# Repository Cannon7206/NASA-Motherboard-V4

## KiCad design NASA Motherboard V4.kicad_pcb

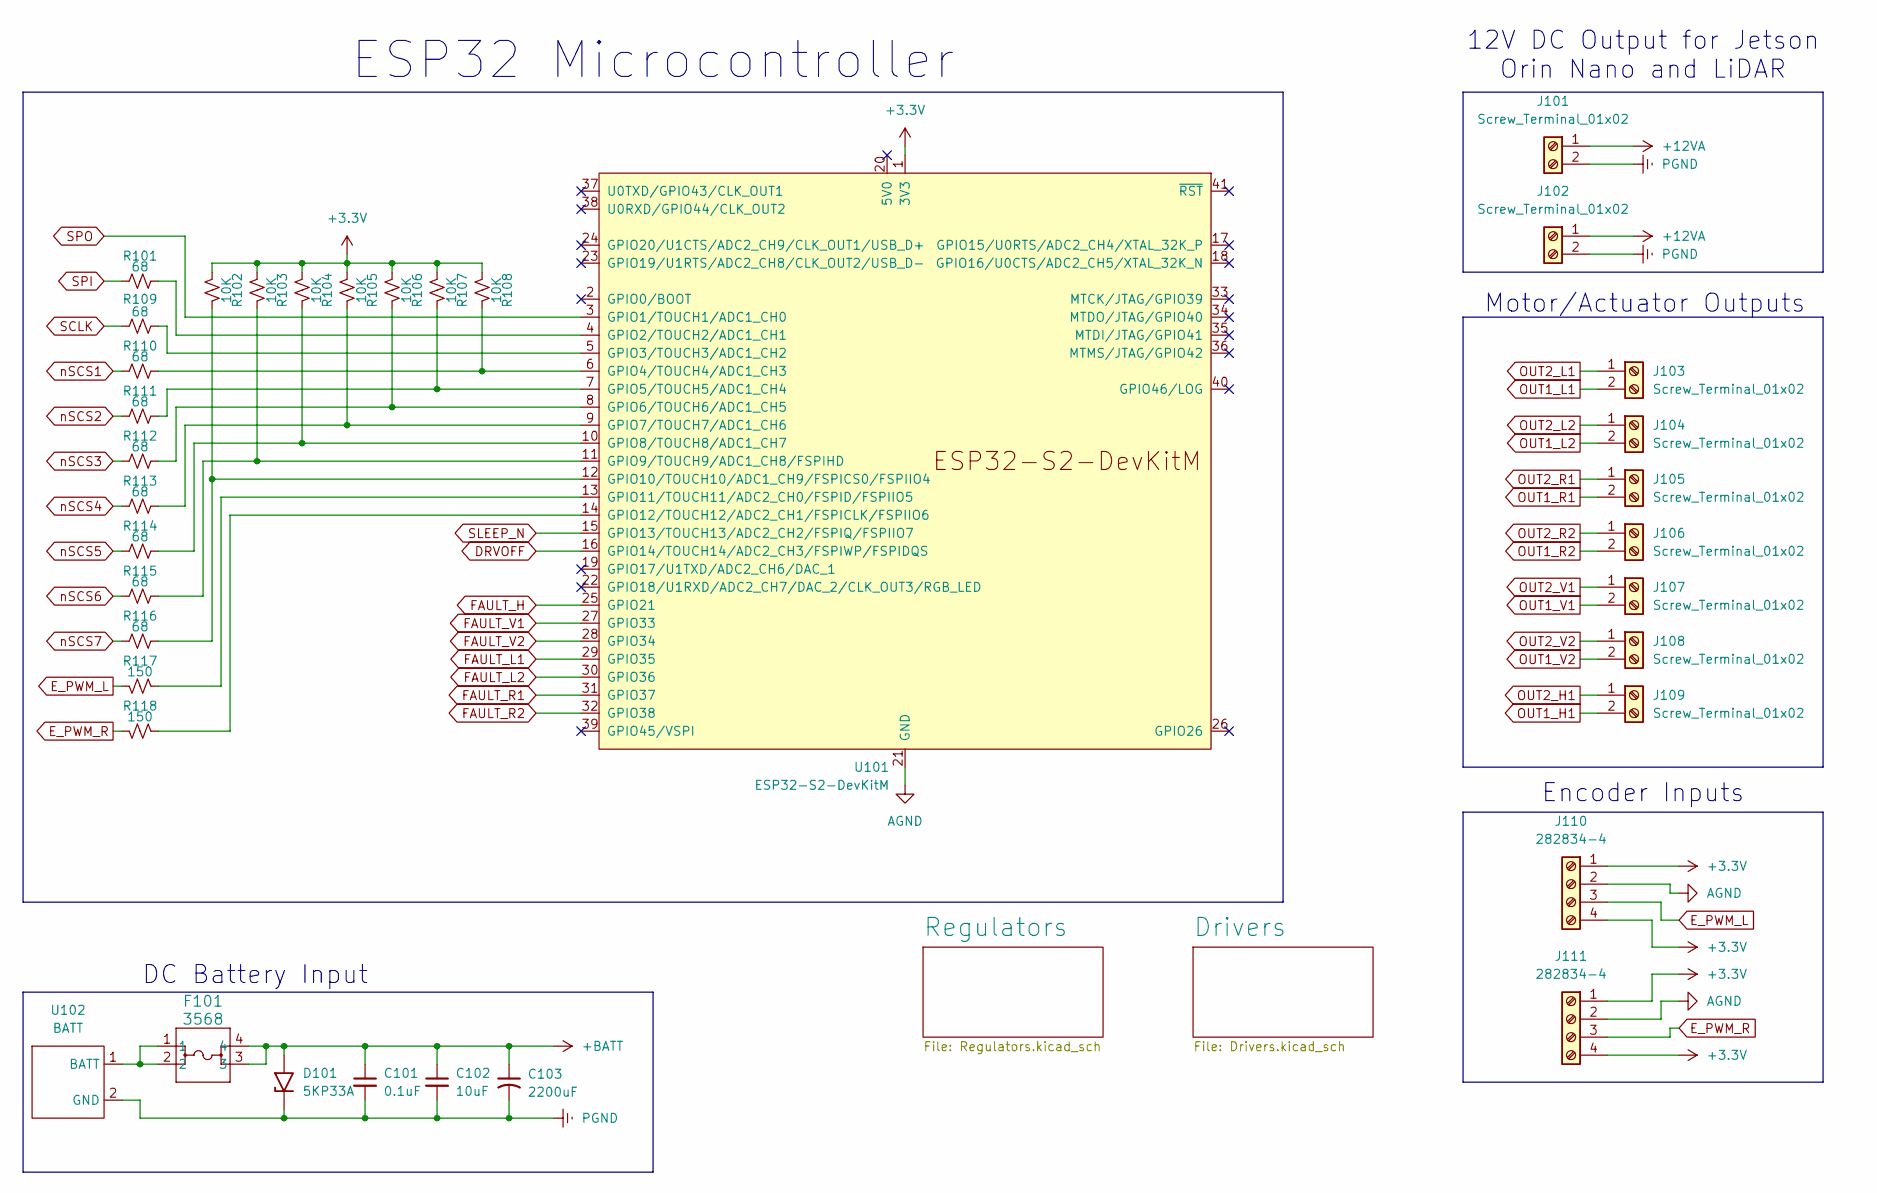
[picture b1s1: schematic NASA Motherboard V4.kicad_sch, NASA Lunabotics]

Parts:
C101: 0.1uF; C_0402_1005Metric_Pad0.74x0.62mm_HandSolder
C102: 10uF; C_1206_3216Metric_Pad1.33x1.80mm_HandSolder
C103: 2200uF; CP_Radial_D16.0mm_P7.50mm
D101: 5KP33A; D_P600_R-6_P20.00mm_Horizontal
F101: 3568; 3568_KEY
J101, J102: Screw_Terminal_01x02; TerminalBlock_TE_282834-2_1x02_P2.54mm_Horizontal; MFR Part # 282834-2
J103, J104, J105, J106, J107, J108, J109: Screw_Terminal_01x02; TerminalBlock_TE_282834-2_1x02_P2.54mm_Horizontal
J110, J111: 282834-4; TerminalBlock_TE_282834-4_1x04_P2.54mm_Horizontal; MFR Part # 282834-4
R101, R109, R110, R111, R112, R113, R114, R115, R116: 68; R_0402_1005Metric_Pad0.72x0.64mm_HandSolder
R102, R103, R104, R105, R106, R107, R108: 10K; R_0603_1608Metric_Pad0.98x0.95mm_HandSolder
R117, R118: 150; R_0603_1608Metric_Pad0.98x0.95mm_HandSolder
U101: ESP32-S2-DevKitM
U102: BATT; Battery Input

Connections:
+3.3V: J110.1, J110.4, J111.1, J111.4, R102.2, R103.2, R104.2, R105.2, R106.2, R107.2, R108.2, U101.1 (3V3); also elsewhere on the board
+12VA: J101.1, J102.1; also elsewhere on the board
+BATT: C101.1, C102.1, C103.1, D101.2 (A2), F101.3, F101.4; also elsewhere on the board
AGND: J110.2, J111.2, U101.21 (GND), U101.42 (GND); also elsewhere on the board
DRVOFF: U101.16 (GPIO14/TOUCH14/ADC2_CH3/FSPIWP/FSPIDQS); also elsewhere on the board
E_PWM_L: J110.3, R117.2
E_PWM_R: J111.3, R118.2
FAULT_H: U101.25 (GPIO21); also elsewhere on the board
FAULT_L1: U101.29 (GPIO35); also elsewhere on the board
FAULT_L2: U101.30 (GPIO36); also elsewhere on the board
FAULT_R1: U101.31 (GPIO37); also elsewhere on the board
FAULT_R2: U101.32 (GPIO38); also elsewhere on the board
FAULT_V1: U101.27 (GPIO33); also elsewhere on the board
FAULT_V2: U101.28 (GPIO34); also elsewhere on the board
unnamed: R101.2, U101.4 (GPIO2/TOUCH2/ADC1_CH1)
unnamed: R109.2, U101.5 (GPIO3/TOUCH3/ADC1_CH2)
unnamed: R108.1, R110.2, U101.6 (GPIO4/TOUCH4/ADC1_CH3)
unnamed: R107.1, R111.2, U101.7 (GPIO5/TOUCH5/ADC1_CH4)
unnamed: R106.1, R112.2, U101.8 (GPIO6/TOUCH6/ADC1_CH5)
unnamed: R105.1, R113.2, U101.9 (GPIO7/TOUCH7/ADC1_CH6)
unnamed: R104.1, R114.2, U101.10 (GPIO8/TOUCH8/ADC1_CH7)
unnamed: R103.1, R115.2, U101.11 (GPIO9/TOUCH9/ADC1_CH8/FSPIHD)
unnamed: R102.1, R116.2, U101.12 (GPIO10/TOUCH10/ADC1_CH9/FSPICS0/FSPIIO4)
unnamed: R117.1, U101.13 (GPIO11/TOUCH11/ADC2_CH0/FSPID/FSPIIO5)
unnamed: R118.1, U101.14 (GPIO12/TOUCH12/ADC2_CH1/FSPICLK/FSPIIO6)
unnamed: F101.1, F101.2, U102.1 (BATT)
OUT1_H1: J109.2; also elsewhere on the board
OUT1_L1: J103.2; also elsewhere on the board
OUT1_L2: J104.2; also elsewhere on the board
OUT1_R1: J105.2; also elsewhere on the board
OUT1_R2: J106.2; also elsewhere on the board
OUT1_V1: J107.2; also elsewhere on the board
OUT1_V2: J108.2; also elsewhere on the board
OUT2_H1: J109.1; also elsewhere on the board
OUT2_L1: J103.1; also elsewhere on the board
OUT2_L2: J104.1; also elsewhere on the board
OUT2_R1: J105.1; also elsewhere on the board
OUT2_R2: J106.1; also elsewhere on the board
OUT2_V1: J107.1; also elsewhere on the board
OUT2_V2: J108.1; also elsewhere on the board
PGND: C101.2, C102.2, C103.2, D101.1 (A1), J101.2, J102.2, U102.2 (GND); also elsewhere on the board
SCLK: R109.1; also elsewhere on the board
SLEEP_N: U101.15 (GPIO13/TOUCH13/ADC2_CH2/FSPIQ/FSPIIO7); also elsewhere on the board
SPI: R101.1; also elsewhere on the board
SPO: U101.3 (GPIO1/TOUCH1/ADC1_CH0); also elsewhere on the board
nSCS1: R110.1; also elsewhere on the board
nSCS2: R111.1; also elsewhere on the board
nSCS3: R112.1; also elsewhere on the board
nSCS4: R113.1; also elsewhere on the board
nSCS5: R114.1; also elsewhere on the board
nSCS6: R115.1; also elsewhere on the board
nSCS7: R116.1; also elsewhere on the board

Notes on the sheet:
Encoder Inputs
DC Battery Input
12V DC Output for Jetson Orin Nano and LiDAR
Motor/Actuator Outputs
ESP32 Microcontroller

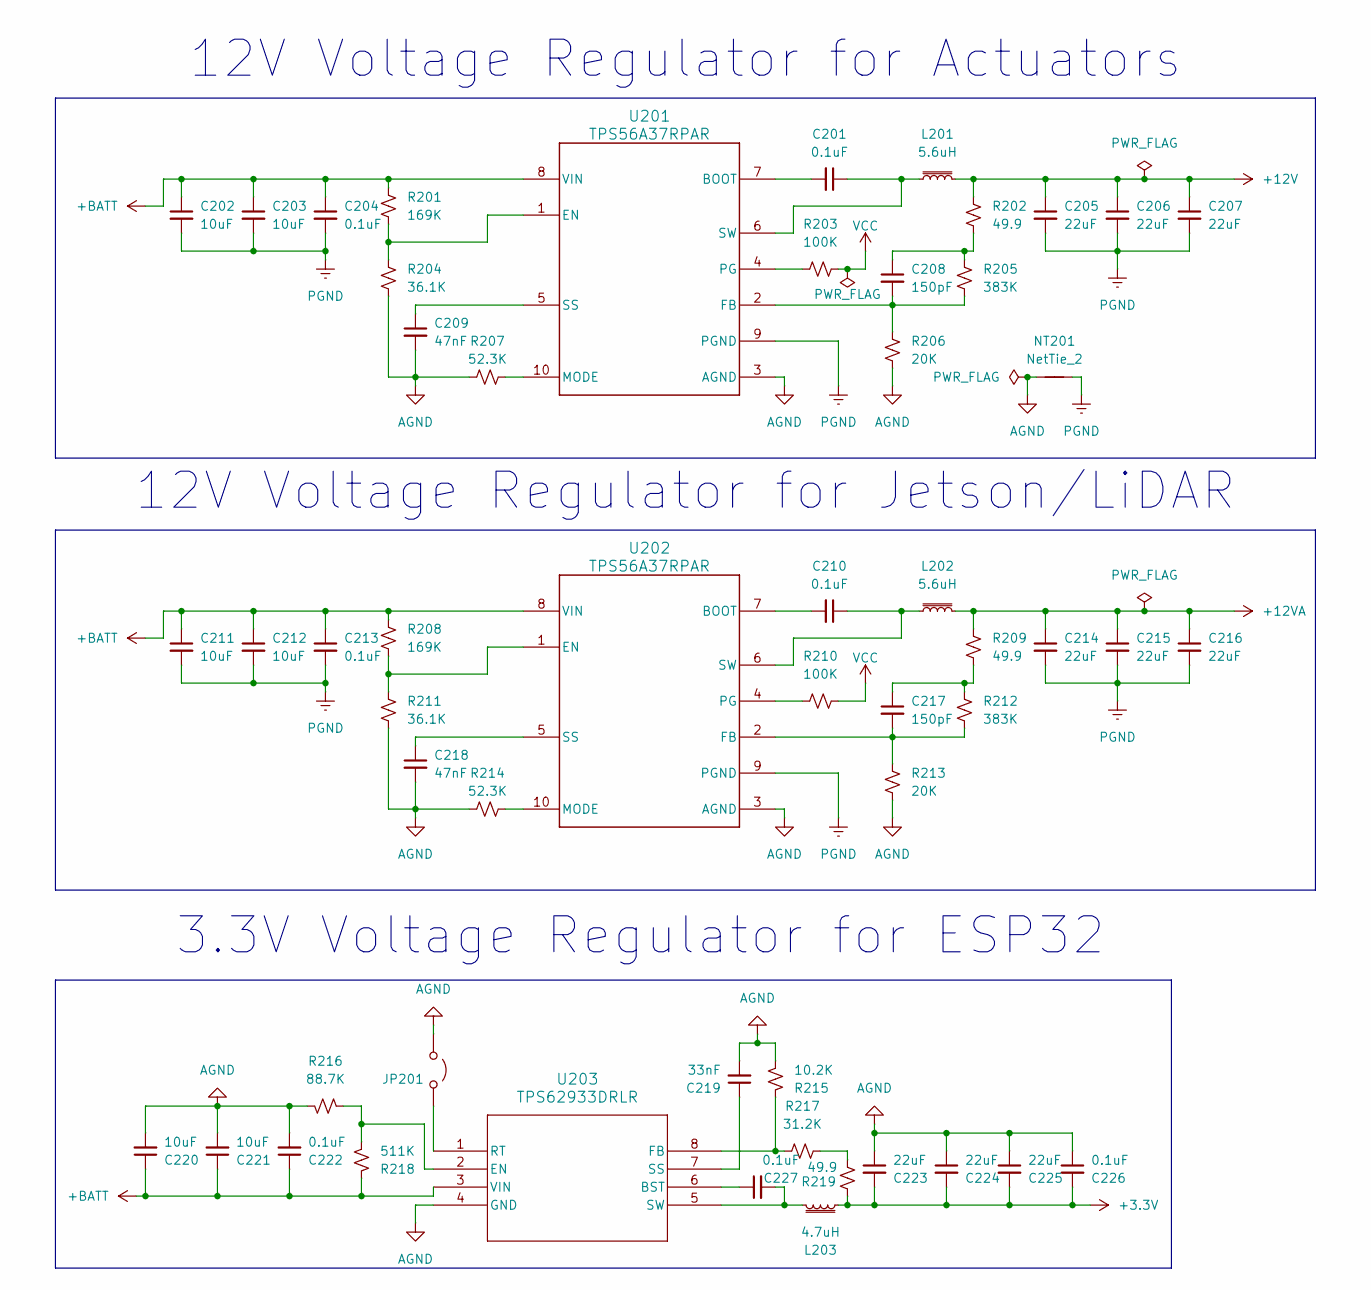
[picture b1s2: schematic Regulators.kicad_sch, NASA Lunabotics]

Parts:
C201, C204, C210, C213, C222, C226, C227: 0.1uF; C_0402_1005Metric_Pad0.74x0.62mm_HandSolder
C202, C203, C211, C212, C220, C221: 10uF; C_1206_3216Metric_Pad1.33x1.80mm_HandSolder
C205, C206, C207, C214, C215, C216, C223, C224, C225: 22uF; C_1210_3225Metric_Pad1.33x2.70mm_HandSolder
C208, C217: 150pF; C_0402_1005Metric_Pad0.74x0.62mm_HandSolder
C209, C218: 47nF; C_0603_1608Metric_Pad1.08x0.95mm_HandSolder
C219: 33nF; C_0603_1608Metric_Pad1.08x0.95mm_HandSolder
JP201: Jumper_2_Open; SolderJumper-2_P1.3mm_Open_Pad1.0x1.5mm
L201, L202: 5.6uH; IND_IHLP-6767DZ_VIS-M
L203: 4.7uH; IND_SRP6530A_BRN-M
NT201: NetTie_2; NetTie-2_THT_Pad1.0mm
R201, R208: 169K; R_0603_1608Metric_Pad0.98x0.95mm_HandSolder
R202, R209, R219: 49.9; R_0402_1005Metric_Pad0.72x0.64mm_HandSolder
R203, R210: 100K; R_0603_1608Metric_Pad0.98x0.95mm_HandSolder
R204, R211: 36.1K; R_0603_1608Metric_Pad0.98x0.95mm_HandSolder
R205, R212: 383K; R_0603_1608Metric_Pad0.98x0.95mm_HandSolder
R206, R213: 20K; R_0603_1608Metric_Pad0.98x0.95mm_HandSolder
R207, R214: 52.3K; R_0603_1608Metric_Pad0.98x0.95mm_HandSolder
R215: 10.2K; R_0603_1608Metric_Pad0.98x0.95mm_HandSolder
R216: 88.7K; R_0603_1608Metric_Pad0.98x0.95mm_HandSolder
R217: 31.2K; R_0603_1608Metric_Pad0.98x0.95mm_HandSolder
R218: 511K; R_0603_1608Metric_Pad0.98x0.95mm_HandSolder
U201, U202: TPS56A37RPAR; RPA0010A-MFG
U203: TPS62933DRLR; SOT-5X3-8_DRL_TEX

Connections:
+3.3V: C223.2, C224.2, C225.2, C226.2, L203.2, R219.1; also elsewhere on the board
+12V: C205.1, C206.1, C207.1, L201.2, R202.1; also elsewhere on the board
+12VA: C214.1, C215.1, C216.1, L202.2, R209.1; also elsewhere on the board
+BATT: C202.1, C203.1, C204.1, C211.1, C212.1, C213.1, C220.1, C221.1, C222.1, R201.1, R208.1, R218.1, U201.8 (VIN), U202.8 (VIN), U203.3 (VIN); also elsewhere on the board
AGND: C209.2, C218.2, C219.2, C220.2, C221.2, C222.2, C223.1, C224.1, C225.1, C226.1, JP201.1 (A), NT201.1, R204.2, R206.2, R207.2, R211.2, R213.2, R214.2, R215.2, R216.2, U201.3 (AGND), U202.3 (AGND), U203.4 (GND); also elsewhere on the board
unnamed: C208.1, R202.2, R205.1
unnamed: C217.1, R209.2, R212.1
unnamed: JP201.2 (B), U203.1 (RT)
unnamed: R217.2, R219.2
unnamed: C201.2, U201.7 (BOOT)
unnamed: R201.2, R204.1, U201.1 (EN)
unnamed: C208.2, R205.2, R206.1, U201.2 (FB)
unnamed: R207.1, U201.10 (MODE)
unnamed: R203.1, U201.4 (PG)
unnamed: C209.1, U201.5 (SS)
unnamed: C201.1, L201.1, U201.6 (SW)
unnamed: C210.2, U202.7 (BOOT)
unnamed: R208.2, R211.1, U202.1 (EN)
unnamed: C217.2, R212.2, R213.1, U202.2 (FB)
unnamed: R214.1, U202.10 (MODE)
unnamed: R210.1, U202.4 (PG)
unnamed: C218.1, U202.5 (SS)
unnamed: C210.1, L202.1, U202.6 (SW)
unnamed: C227.1, U203.6 (BST)
unnamed: R216.1, R218.2, U203.2 (EN)
unnamed: R215.1, R217.1, U203.8 (FB)
unnamed: C219.1, U203.7 (SS)
unnamed: C227.2, L203.1, U203.5 (SW)
PGND: C202.2, C203.2, C204.2, C205.2, C206.2, C207.2, C211.2, C212.2, C213.2, C214.2, C215.2, C216.2, NT201.2, U201.9 (PGND), U202.9 (PGND); also elsewhere on the board
VCC: R203.2, R210.2

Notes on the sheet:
12V Voltage Regulator for Actuators
3.3V Voltage Regulator for ESP32
12V Voltage Regulator for Jetson/LiDAR

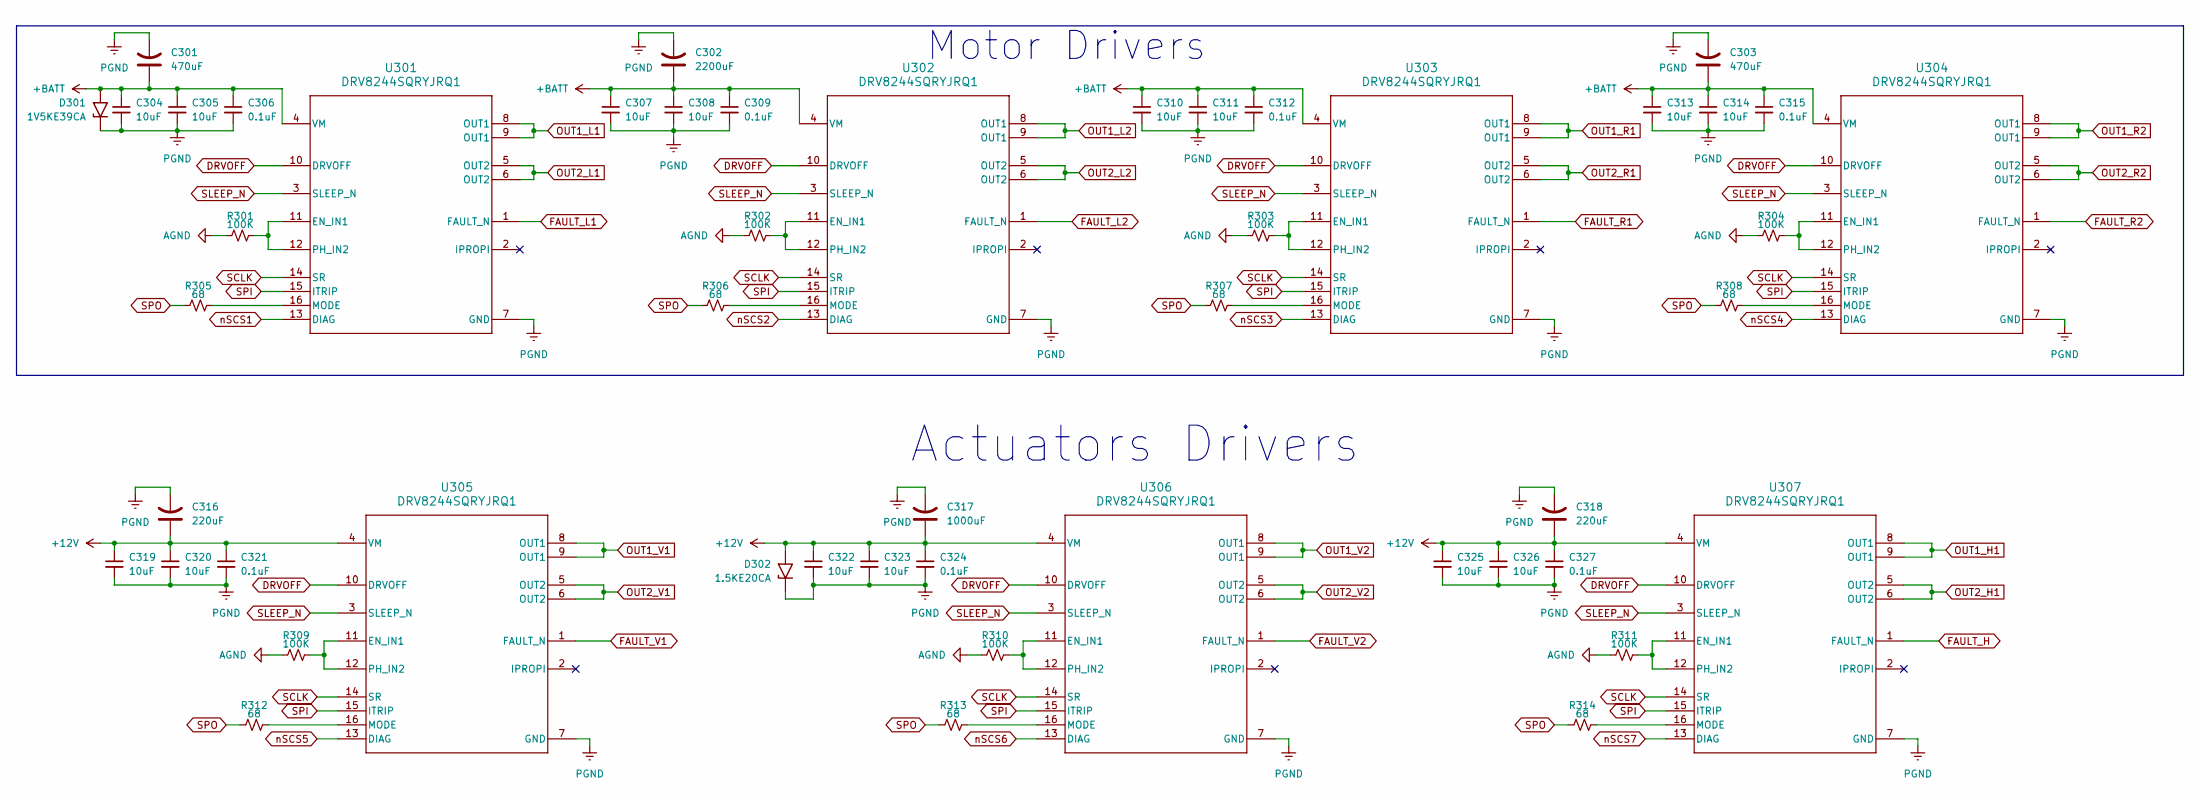
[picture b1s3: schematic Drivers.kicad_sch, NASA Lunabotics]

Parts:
C301, C303: 470uF; CP_Radial_D12.5mm_P5.00mm
C302: 2200uF; CP_Radial_D16.0mm_P7.50mm
C304, C305, C307, C308, C310, C311, C313, C314, C319, C320, C322, C323, C325, C326: 10uF; C_1206_3216Metric_Pad1.33x1.80mm_HandSolder
C306, C309, C312, C315, C321, C324, C327: 0.1uF; C_0402_1005Metric_Pad0.74x0.62mm_HandSolder
C316, C318: 220uF; CP_Radial_D8.0mm_P3.50mm
C317: 1000uF; CP_Radial_D10.0mm_P5.00mm
D301: 1V5KE39CA; D_DO-201AE_P15.24mm_Horizontal
D302: 1.5KE20CA; D_DO-201AE_P15.24mm_Horizontal
R301, R302, R303, R304, R309, R310, R311: 100K; R_0402_1005Metric_Pad0.72x0.64mm_HandSolder
R305, R306, R307, R308, R312, R313, R314: 68; R_0402_1005Metric_Pad0.72x0.64mm_HandSolder
U301, U302, U303, U304, U305, U306, U307: DRV8244SQRYJRQ1; RYJ0016A-MFG

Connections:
+12V: C316.1, C317.1, C318.1, C319.1, C320.1, C321.1, C322.1, C323.1, C324.1, C325.1, C326.1, C327.1, D302.2 (A2), U305.4 (VM), U306.4 (VM), U307.4 (VM); also elsewhere on the board
+BATT: C301.1, C302.1, C303.1, C304.1, C305.1, C306.1, C307.1, C308.1, C309.1, C310.1, C311.1, C312.1, C313.1, C314.1, C315.1, D301.2 (A2), U301.4 (VM), U302.4 (VM), U303.4 (VM), U304.4 (VM); also elsewhere on the board
AGND: R301.1, R302.1, R303.1, R304.1, R309.1, R310.1, R311.1; also elsewhere on the board
DRVOFF: U301.10 (DRVOFF), U302.10 (DRVOFF), U303.10 (DRVOFF), U304.10 (DRVOFF), U305.10 (DRVOFF), U306.10 (DRVOFF), U307.10 (DRVOFF); also elsewhere on the board
FAULT_H: U307.1 (FAULT_N); also elsewhere on the board
FAULT_L1: U301.1 (FAULT_N); also elsewhere on the board
FAULT_L2: U302.1 (FAULT_N); also elsewhere on the board
FAULT_R1: U303.1 (FAULT_N); also elsewhere on the board
FAULT_R2: U304.1 (FAULT_N); also elsewhere on the board
FAULT_V1: U305.1 (FAULT_N); also elsewhere on the board
FAULT_V2: U306.1 (FAULT_N); also elsewhere on the board
unnamed: R301.2, U301.11 (EN_IN1), U301.12 (PH_IN2)
unnamed: R305.2, U301.16 (MODE)
unnamed: R302.2, U302.11 (EN_IN1), U302.12 (PH_IN2)
unnamed: R306.2, U302.16 (MODE)
unnamed: R303.2, U303.11 (EN_IN1), U303.12 (PH_IN2)
unnamed: R307.2, U303.16 (MODE)
unnamed: R304.2, U304.11 (EN_IN1), U304.12 (PH_IN2)
unnamed: R308.2, U304.16 (MODE)
unnamed: R309.2, U305.11 (EN_IN1), U305.12 (PH_IN2)
unnamed: R312.2, U305.16 (MODE)
unnamed: R310.2, U306.11 (EN_IN1), U306.12 (PH_IN2)
unnamed: R313.2, U306.16 (MODE)
unnamed: R311.2, U307.11 (EN_IN1), U307.12 (PH_IN2)
unnamed: R314.2, U307.16 (MODE)
OUT1_H1: U307.8 (OUT1), U307.9 (OUT1); also elsewhere on the board
OUT1_L1: U301.8 (OUT1), U301.9 (OUT1); also elsewhere on the board
OUT1_L2: U302.8 (OUT1), U302.9 (OUT1); also elsewhere on the board
OUT1_R1: U303.8 (OUT1), U303.9 (OUT1); also elsewhere on the board
OUT1_R2: U304.8 (OUT1), U304.9 (OUT1); also elsewhere on the board
OUT1_V1: U305.8 (OUT1), U305.9 (OUT1); also elsewhere on the board
OUT1_V2: U306.8 (OUT1), U306.9 (OUT1); also elsewhere on the board
OUT2_H1: U307.5 (OUT2), U307.6 (OUT2); also elsewhere on the board
OUT2_L1: U301.5 (OUT2), U301.6 (OUT2); also elsewhere on the board
OUT2_L2: U302.5 (OUT2), U302.6 (OUT2); also elsewhere on the board
OUT2_R1: U303.5 (OUT2), U303.6 (OUT2); also elsewhere on the board
OUT2_R2: U304.5 (OUT2), U304.6 (OUT2); also elsewhere on the board
OUT2_V1: U305.5 (OUT2), U305.6 (OUT2); also elsewhere on the board
OUT2_V2: U306.5 (OUT2), U306.6 (OUT2); also elsewhere on the board
PGND: C301.2, C302.2, C303.2, C304.2, C305.2, C306.2, C307.2, C308.2, C309.2, C310.2, C311.2, C312.2, C313.2, C314.2, C315.2, C316.2, C317.2, C318.2, C319.2, C320.2, C321.2, C322.2, C323.2, C324.2, C325.2, C326.2, C327.2, D301.1 (A1), D302.1 (A1), U301.7 (GND), U302.7 (GND), U303.7 (GND), U304.7 (GND), U305.7 (GND), U306.7 (GND), U307.7 (GND); also elsewhere on the board
SCLK: U301.14 (SR), U302.14 (SR), U303.14 (SR), U304.14 (SR), U305.14 (SR), U306.14 (SR), U307.14 (SR); also elsewhere on the board
SLEEP_N: U301.3 (SLEEP_N), U302.3 (SLEEP_N), U303.3 (SLEEP_N), U304.3 (SLEEP_N), U305.3 (SLEEP_N), U306.3 (SLEEP_N), U307.3 (SLEEP_N); also elsewhere on the board
SPI: U301.15 (ITRIP), U302.15 (ITRIP), U303.15 (ITRIP), U304.15 (ITRIP), U305.15 (ITRIP), U306.15 (ITRIP), U307.15 (ITRIP); also elsewhere on the board
SPO: R305.1, R306.1, R307.1, R308.1, R312.1, R313.1, R314.1; also elsewhere on the board
nSCS1: U301.13 (DIAG); also elsewhere on the board
nSCS2: U302.13 (DIAG); also elsewhere on the board
nSCS3: U303.13 (DIAG); also elsewhere on the board
nSCS4: U304.13 (DIAG); also elsewhere on the board
nSCS5: U305.13 (DIAG); also elsewhere on the board
nSCS6: U306.13 (DIAG); also elsewhere on the board
nSCS7: U307.13 (DIAG); also elsewhere on the board

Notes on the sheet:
Motor Drivers
Actuators Drivers

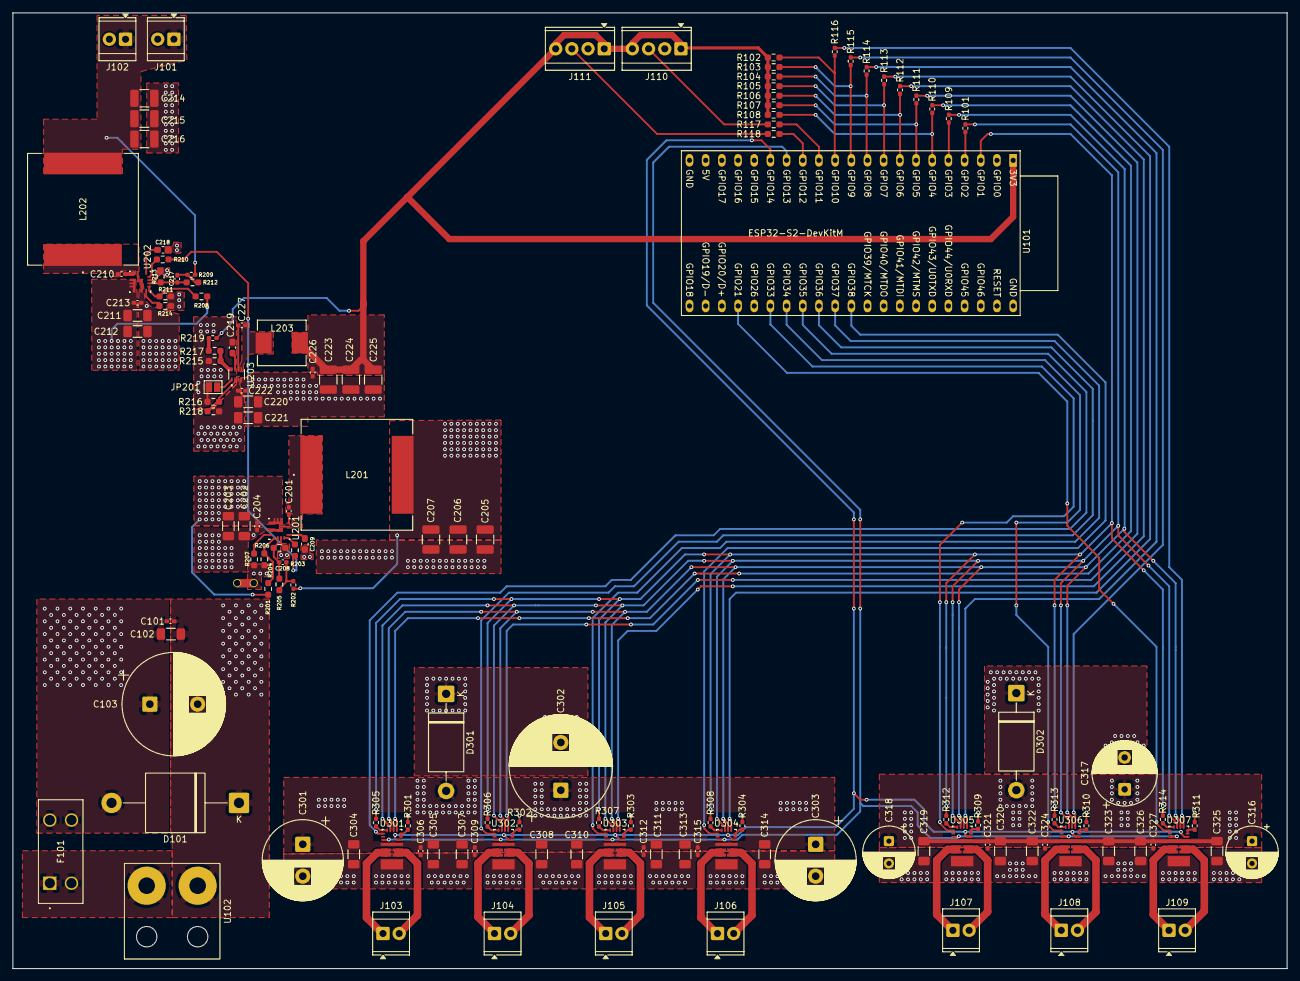
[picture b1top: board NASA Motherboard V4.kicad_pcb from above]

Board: 6 copper layers, 200.0 x 150.0 mm, 140 parts (0 on the bottom side), 91 nets.

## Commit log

2026-01-29 Updated settings
2026-01-30 Minor changes
2026-01-30 Adding gitignore to properly ignore unwanted items
2026-01-30 Reorganizing the filetree structure
2026-01-30 Fixed libraries
